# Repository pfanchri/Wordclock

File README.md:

# Wordclock
Mein Projekt für die DIY Vorlesung an der FAU Erlangen

Ziel des Projektes war es eine Wordclock zu erstellen, die kleiner als alle gewöhnlichen Wordclocks ist und als Tischuhr 
fungieren soll. Als Vorbild diente das Modell von qlocktwo. 

Die Uhr kann nicht nur die Zeit anzeigen, sonder speichert auch den Wochentag, dieser wird in der aktuellen Softwareversion 
aber noch nicht angezeigt. Weitere Verbesserungen sind etwa ein Batteriebuffer und weitere Möglichkeiten für die Frontplatte.

Bei der Vorlesung DIY gab es auch ein Wiki für alle Projekte. Das Wordlcock-Projekt ist unter folgendem Link zu finden: 
http://faui7pi.informatik.uni-erlangen.de/mediawiki/index.php/Wordclock

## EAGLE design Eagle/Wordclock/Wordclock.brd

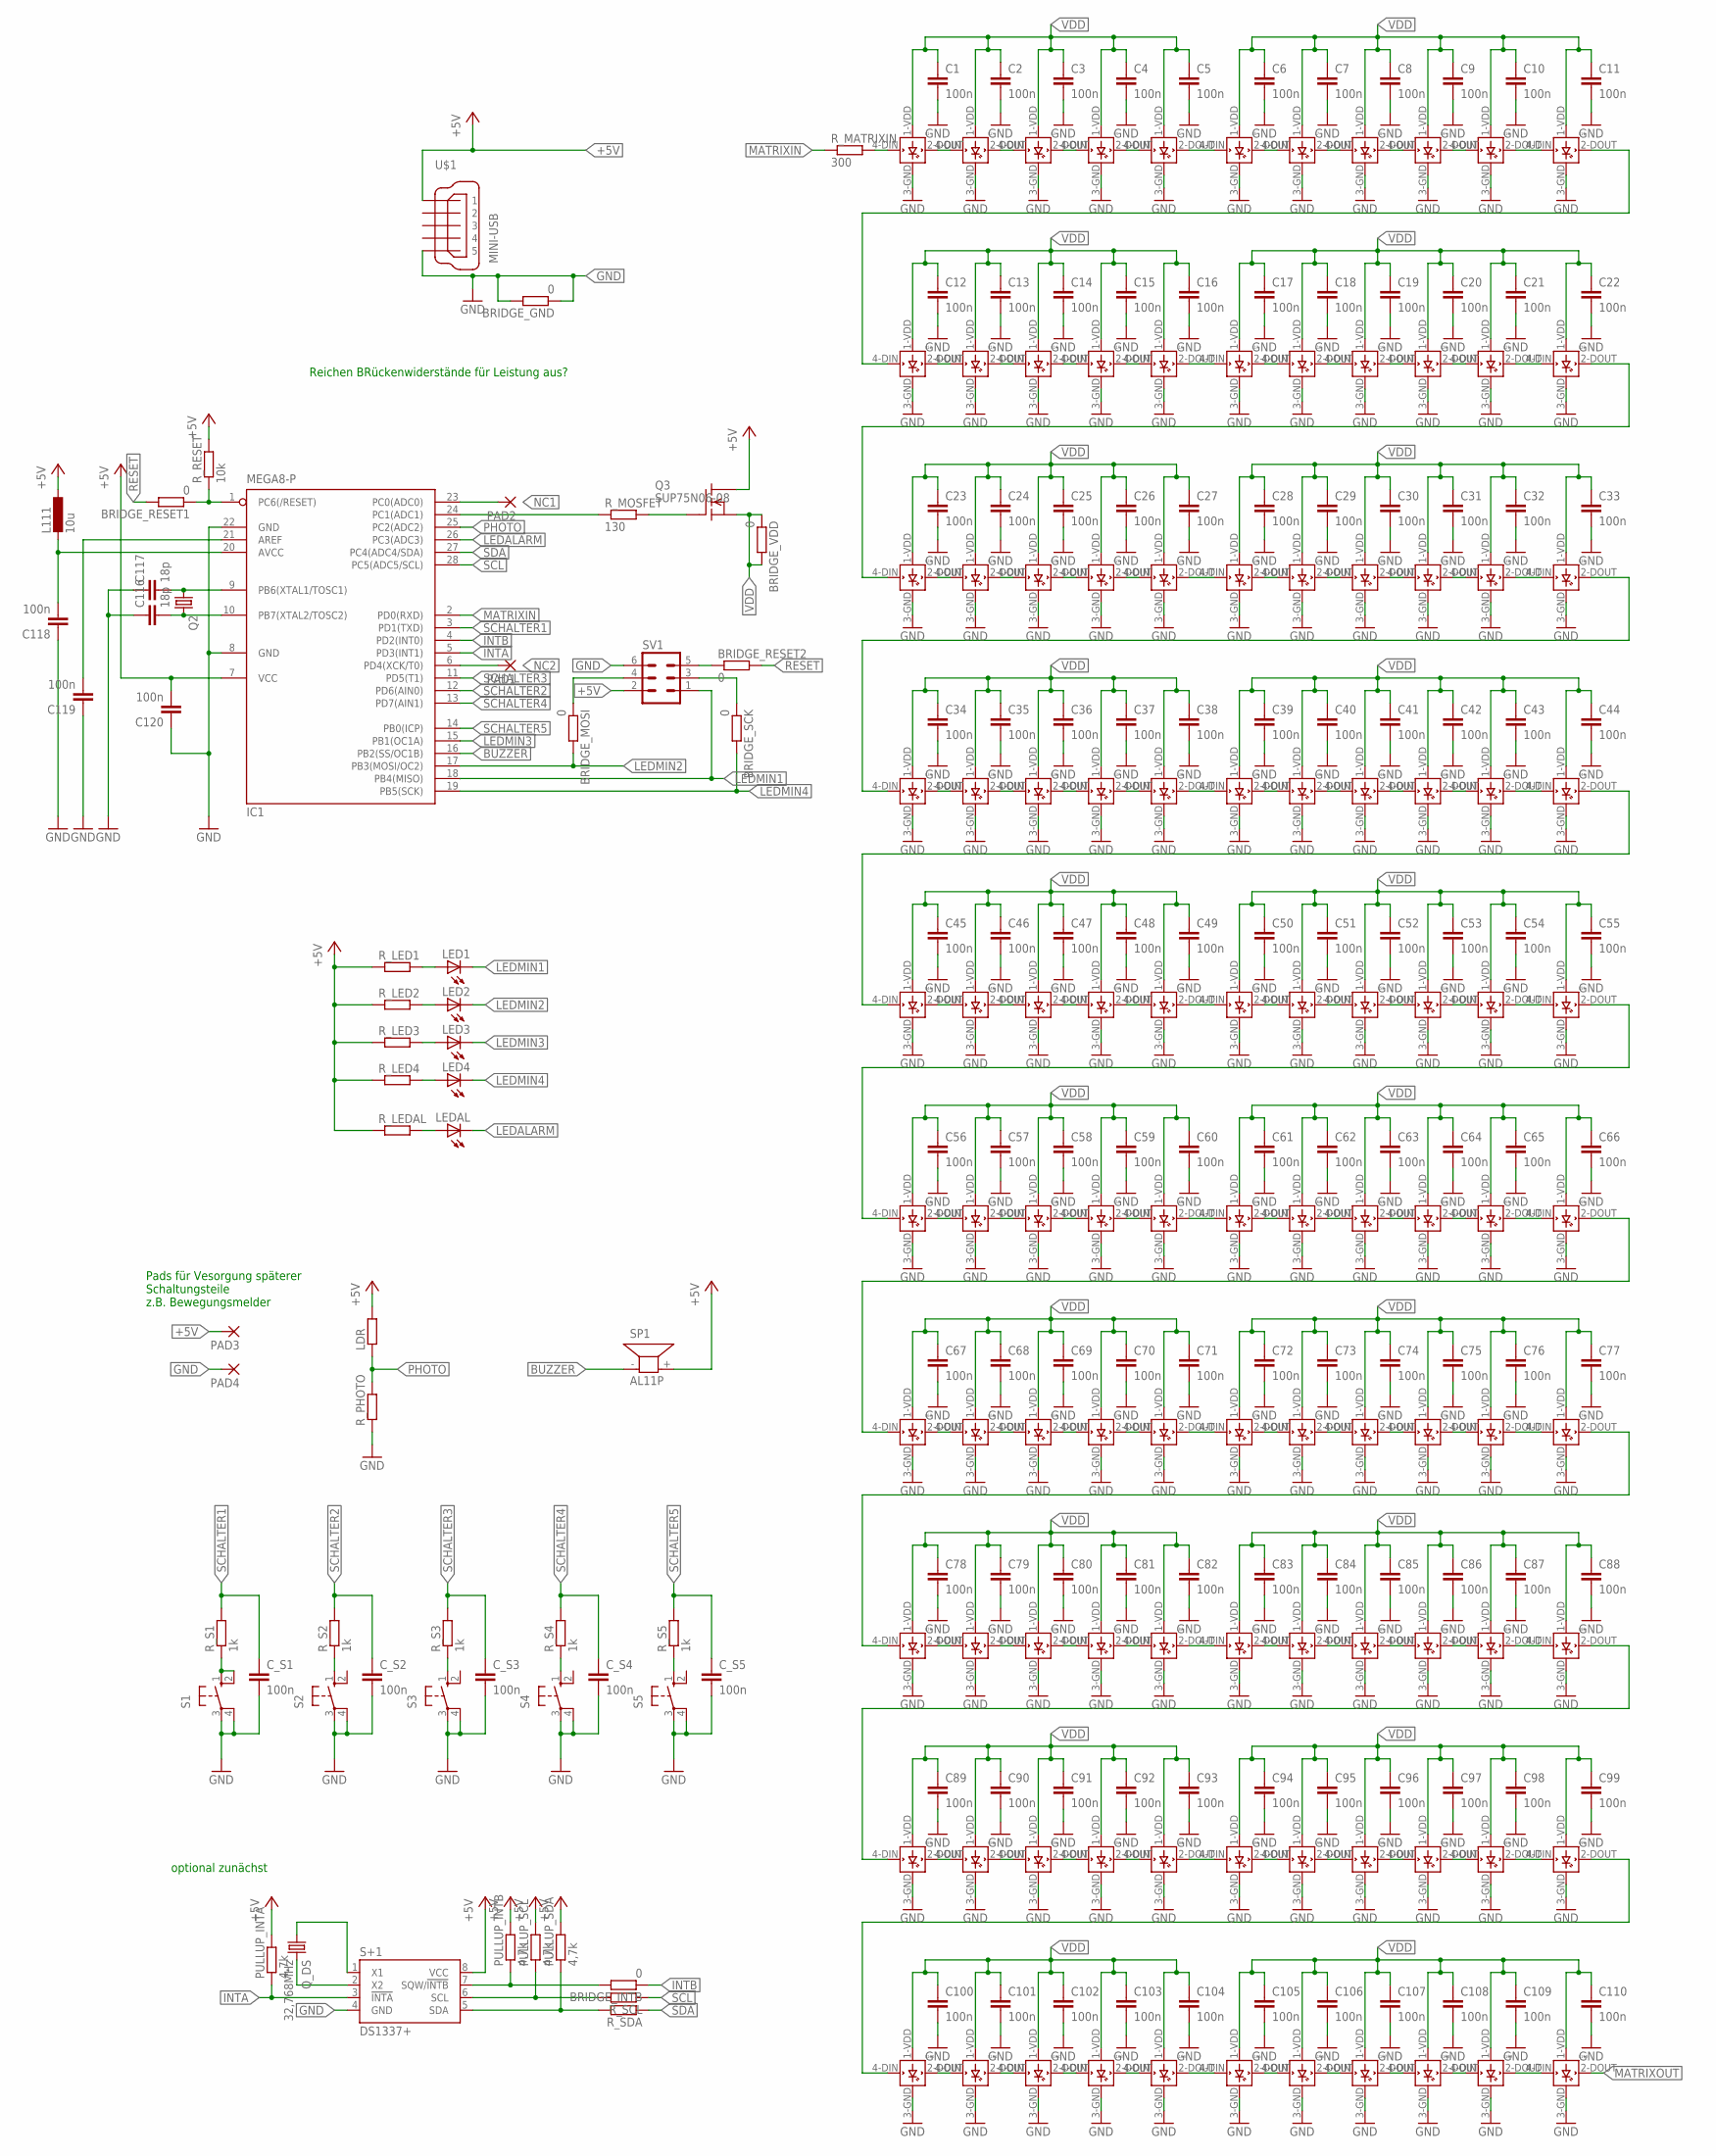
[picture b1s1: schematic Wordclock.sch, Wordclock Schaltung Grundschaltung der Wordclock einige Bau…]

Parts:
BRIDGE_GND: 0; R1206
BRIDGE_INTB: 0; R1206
BRIDGE_MOSI: 0; R1206
BRIDGE_RESET1: 0; M1206
BRIDGE_RESET2: 0; R1206
BRIDGE_SCK: 0; R1206
BRIDGE_VDD: 0; R1206
C1, C2, C3, C4, C5, C6, C7, C8, C9, C10, C11, C12, C13, C14, C15, C16, C17, C18, C19, C20, C21, C22, C23, C24, C25, C26, C27, C28, C29, C30, C31, C32, C33, C34, C35, C36, C37, C38, C39, C40, C41, C42, C43, C44, C45, C46, C47, C48, C49, C50, C51, C52, C53, C54, C55, C56, C57, C58, C59, C60, C61, C62, C63, C64, C65, C66, C67, C68, C69, C70, C71, C72, C73, C74, C75, C76, C77, C78, C79, C80, C81, C82, C83, C84, C85, C86, C87, C88, C89, C90, C91, C92, C93, C94, C95, C96, C97, C98, C99, C100, C101, C102, C103, C104, C105, C106, C107, C108, C109, C110: 100n; C1310
C116, C117: 18p; C0805
C118: 100n; C1206
C119, C120: 100n; C0805
C_S1, C_S2, C_S3, C_S4, C_S5: 100n; C1206
IC1: MEGA8-P; DIL28-3
L1, L2, L3, L4, L5, L6, L7, L8, L9, L10, L11, L12, L13, L14, L15, L16, L17, L18, L19, L20, L21, L22, L23, L24, L25, L26, L27, L28, L29, L30, L31, L32, L33, L34, L35, L36, L37, L38, L39, L40, L41, L42, L43, L44, L45, L46, L47, L48, L49, L50, L51, L52, L53, L54, L55, L56, L57, L58, L59, L60, L61, L62, L63, L64, L65, L66, L67, L68, L69, L70, L71, L72, L73, L74, L75, L76, L77, L78, L79, L80, L81, L82, L83, L84, L85, L86, L87, L88, L89, L90, L91, L92, L93, L94, L95, L96, L97, L98, L99, L100, L101, L102, L103, L104, L105, L106, L107, L108, L109, L110: WS2812B
L111: 10u; L2012C
LDR: R-EU_0204/5; 0204/5
LED1, LED2, LED3, LED4: LEDCHIPLED_1206; CHIPLED_1206
LEDAL: LEDCHIPLED_1206; CHIPLED_1206
PAD1, PAD2, PAD3, PAD4: 2,54/1,1
PULLUP_INTA: 4,7k; R1206
PULLUP_INTB: 4,7k; R1206
PULLUP_SCL: 4,7k; R1206
PULLUP_SDA: 4,7k; R1206
Q2: CRYSTALHC49S; HC49/S
Q3: SUP75N06-08; TO220
Q_DS: 32,768MHz; HC49/S
R_LED1, R_LED2, R_LED3, R_LED4: R-EU_M1206; M1206
R_LEDAL: R-EU_M1206; M1206
R_MATRIXIN: 300; R1206
R_MOSFET: 130; R1206
R_PHOTO: R-EU_M1206; M1206
R_RESET: 10k; M1206
R_S1, R_S2, R_S3, R_S4, R_S5: 1k; M1206
R_SCL: R-EU_R1206; R1206
R_SDA: R-EU_R1206; R1206
S1, S2, S3, S4, S5: 10-XX; B3F-10XX
S+1: DS1337+; DIL8
SP1: AL11P
SV1: ML6L
U$1: MINI-USB

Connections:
+5V: C120.2, IC1.7 (VCC), L111.1, LDR.2, PAD3.1, PULLUP_INTA.2, PULLUP_INTB.2, PULLUP_SCL.2, PULLUP_SDA.2, Q3.2 (D), R_LED1.1, R_LED2.1, R_LED3.1, R_LED4.1, R_LEDAL.1, R_RESET.2, S+1.8 (VCC), SP1.+ (2), SV1.2, U$1.1
BUZZER: IC1.16 (PB2(SS/OC1B)), SP1.- (1)
GND: BRIDGE_GND.1, BRIDGE_GND.2, C1.2, C2.2, C3.2, C4.2, C5.2, C6.2, C7.2, C8.2, C9.2, C10.2, C11.2, C12.2, C13.2, C14.2, C15.2, C16.2, C17.2, C18.2, C19.2, C20.2, C21.2, C22.2, C23.2, C24.2, C25.2, C26.2, C27.2, C28.2, C29.2, C30.2, C31.2, C32.2, C33.2, C34.2, C35.2, C36.2, C37.2, C38.2, C39.2, C40.2, C41.2, C42.2, C43.2, C44.2, C45.2, C46.2, C47.2, C48.2, C49.2, C50.2, C51.2, C52.2, C53.2, C54.2, C55.2, C56.2, C57.2, C58.2, C59.2, C60.2, C61.2, C62.2, C63.2, C64.2, C65.2, C66.2, C67.2, C68.2, C69.2, C70.2, C71.2, C72.2, C73.2, C74.2, C75.2, C76.2, C77.2, C78.2, C79.2, C80.2, C81.2, C82.2, C83.2, C84.2, C85.2, C86.2, C87.2, C88.2, C89.2, C90.2, C91.2, C92.2, C93.2, C94.2, C95.2, C96.2, C97.2, C98.2, C99.2, C100.2, C101.2, C102.2, C103.2, C104.2, C105.2, C106.2, C107.2, C108.2, C109.2, C110.2, C116.1, C117.1, C118.1, C119.1, C120.1, C_S1.2, C_S2.2, C_S3.2, C_S4.2, C_S5.2, IC1.8 (GND), IC1.22 (GND), L1.3-GND (GND), L2.3-GND (GND), L3.3-GND (GND), L4.3-GND (GND), L5.3-GND (GND), L6.3-GND (GND), L7.3-GND (GND), L8.3-GND (GND), L9.3-GND (GND), L10.3-GND (GND), L11.3-GND (GND), L12.3-GND (GND), L13.3-GND (GND), L14.3-GND (GND), L15.3-GND (GND), L16.3-GND (GND), L17.3-GND (GND), L18.3-GND (GND), L19.3-GND (GND), L20.3-GND (GND), L21.3-GND (GND), L22.3-GND (GND), L23.3-GND (GND), L24.3-GND (GND), L25.3-GND (GND), L26.3-GND (GND), L27.3-GND (GND), L28.3-GND (GND), L29.3-GND (GND), L30.3-GND (GND), L31.3-GND (GND), L32.3-GND (GND), L33.3-GND (GND), L34.3-GND (GND), L35.3-GND (GND), L36.3-GND (GND), L37.3-GND (GND), L38.3-GND (GND), L39.3-GND (GND), L40.3-GND (GND), L41.3-GND (GND), L42.3-GND (GND), L43.3-GND (GND), L44.3-GND (GND), L45.3-GND (GND), L46.3-GND (GND), L47.3-GND (GND), L48.3-GND (GND), L49.3-GND (GND), L50.3-GND (GND), L51.3-GND (GND), L52.3-GND (GND), L53.3-GND (GND), L54.3-GND (GND), L55.3-GND (GND), L56.3-GND (GND), L57.3-GND (GND), L58.3-GND (GND), L59.3-GND (GND), L60.3-GND (GND), L61.3-GND (GND), L62.3-GND (GND), L63.3-GND (GND), L64.3-GND (GND), L65.3-GND (GND), L66.3-GND (GND), L67.3-GND (GND), L68.3-GND (GND), L69.3-GND (GND), L70.3-GND (GND), L71.3-GND (GND), L72.3-GND (GND), L73.3-GND (GND), L74.3-GND (GND), L75.3-GND (GND), L76.3-GND (GND), L77.3-GND (GND), L78.3-GND (GND), L79.3-GND (GND), L80.3-GND (GND), L81.3-GND (GND), L82.3-GND (GND), L83.3-GND (GND), L84.3-GND (GND), L85.3-GND (GND), L86.3-GND (GND), L87.3-GND (GND), L88.3-GND (GND), L89.3-GND (GND), L90.3-GND (GND), L91.3-GND (GND), L92.3-GND (GND), L93.3-GND (GND), L94.3-GND (GND), L95.3-GND (GND), L96.3-GND (GND), L97.3-GND (GND), L98.3-GND (GND), L99.3-GND (GND), L100.3-GND (GND), L101.3-GND (GND), L102.3-GND (GND), L103.3-GND (GND), L104.3-GND (GND), L105.3-GND (GND), L106.3-GND (GND), L107.3-GND (GND), L108.3-GND (GND), L109.3-GND (GND), L110.3-GND (GND), PAD4.1, R_PHOTO.1, S1.3, S1.4 (P1), S2.3, S2.4 (P1), S3.3, S3.4 (P1), S4.3, S4.4 (P1), S5.3, S5.4 (P1), S+1.4 (GND), SV1.6, U$1.5
INTA: IC1.5 (PD3(INT1)), PULLUP_INTA.1, S+1.3 (!INTA)
INTB: BRIDGE_INTB.1, IC1.4 (PD2(INT0))
INTB_UNBRIDGED: BRIDGE_INTB.2, PULLUP_INTB.1, S+1.7 (SQW/!INTB!)
LEDALARM: IC1.26 (PC3(ADC3)), LEDAL.C
LEDMIN1: IC1.18 (PB4(MISO)), LED1.C, SV1.1
LEDMIN2: BRIDGE_MOSI.2, IC1.17 (PB3(MOSI/OC2)), LED2.C
LEDMIN3: IC1.15 (PB1(OC1A)), LED3.C
LEDMIN4: BRIDGE_SCK.2, IC1.19 (PB5(SCK)), LED4.C
MATRIXIN: IC1.2 (PD0(RXD)), R_MATRIXIN.1
MATRIXOUT: L110.2-DOUT (DOUT)
MOSFET_A: IC1.24 (PC1(ADC1)), R_MOSFET.1
MOSFET_B: Q3.1 (G), R_MOSFET.2
unnamed: L1.2-DOUT (DOUT), L2.4-DIN (DIN)
unnamed: L2.2-DOUT (DOUT), L3.4-DIN (DIN)
unnamed: L3.2-DOUT (DOUT), L4.4-DIN (DIN)
unnamed: L4.2-DOUT (DOUT), L5.4-DIN (DIN)
unnamed: L6.2-DOUT (DOUT), L7.4-DIN (DIN)
unnamed: L5.2-DOUT (DOUT), L6.4-DIN (DIN)
unnamed: L7.2-DOUT (DOUT), L8.4-DIN (DIN)
unnamed: L8.2-DOUT (DOUT), L9.4-DIN (DIN)
unnamed: L9.2-DOUT (DOUT), L10.4-DIN (DIN)
unnamed: L10.2-DOUT (DOUT), L11.4-DIN (DIN)
unnamed: L12.2-DOUT (DOUT), L13.4-DIN (DIN)
unnamed: L13.2-DOUT (DOUT), L14.4-DIN (DIN)
unnamed: L14.2-DOUT (DOUT), L15.4-DIN (DIN)
unnamed: L15.2-DOUT (DOUT), L16.4-DIN (DIN)
unnamed: L16.2-DOUT (DOUT), L17.4-DIN (DIN)
unnamed: L17.2-DOUT (DOUT), L18.4-DIN (DIN)
unnamed: L18.2-DOUT (DOUT), L19.4-DIN (DIN)
unnamed: L19.2-DOUT (DOUT), L20.4-DIN (DIN)
unnamed: L20.2-DOUT (DOUT), L21.4-DIN (DIN)
unnamed: Q_DS.1, S+1.1 (X1)
unnamed: Q_DS.2, S+1.2 (X2)
unnamed: L21.2-DOUT (DOUT), L22.4-DIN (DIN)
unnamed: L23.2-DOUT (DOUT), L24.4-DIN (DIN)
unnamed: L24.2-DOUT (DOUT), L25.4-DIN (DIN)
unnamed: L25.2-DOUT (DOUT), L26.4-DIN (DIN)
unnamed: L26.2-DOUT (DOUT), L27.4-DIN (DIN)
unnamed: L27.2-DOUT (DOUT), L28.4-DIN (DIN)
unnamed: L28.2-DOUT (DOUT), L29.4-DIN (DIN)
unnamed: L29.2-DOUT (DOUT), L30.4-DIN (DIN)
unnamed: L30.2-DOUT (DOUT), L31.4-DIN (DIN)
unnamed: L31.2-DOUT (DOUT), L32.4-DIN (DIN)
unnamed: L32.2-DOUT (DOUT), L33.4-DIN (DIN)
unnamed: L34.2-DOUT (DOUT), L35.4-DIN (DIN)
unnamed: L35.2-DOUT (DOUT), L36.4-DIN (DIN)
unnamed: L36.2-DOUT (DOUT), L37.4-DIN (DIN)
unnamed: L37.2-DOUT (DOUT), L38.4-DIN (DIN)
unnamed: L38.2-DOUT (DOUT), L39.4-DIN (DIN)
unnamed: L39.2-DOUT (DOUT), L40.4-DIN (DIN)
unnamed: L40.2-DOUT (DOUT), L41.4-DIN (DIN)
unnamed: L41.2-DOUT (DOUT), L42.4-DIN (DIN)
unnamed: L42.2-DOUT (DOUT), L43.4-DIN (DIN)
unnamed: L43.2-DOUT (DOUT), L44.4-DIN (DIN)
unnamed: L45.2-DOUT (DOUT), L46.4-DIN (DIN)
unnamed: L46.2-DOUT (DOUT), L47.4-DIN (DIN)
unnamed: L47.2-DOUT (DOUT), L48.4-DIN (DIN)
unnamed: L48.2-DOUT (DOUT), L49.4-DIN (DIN)
unnamed: L49.2-DOUT (DOUT), L50.4-DIN (DIN)
unnamed: L50.2-DOUT (DOUT), L51.4-DIN (DIN)
unnamed: L51.2-DOUT (DOUT), L52.4-DIN (DIN)
unnamed: L52.2-DOUT (DOUT), L53.4-DIN (DIN)
unnamed: L53.2-DOUT (DOUT), L54.4-DIN (DIN)
unnamed: L54.2-DOUT (DOUT), L55.4-DIN (DIN)
unnamed: L56.2-DOUT (DOUT), L57.4-DIN (DIN)
unnamed: L57.2-DOUT (DOUT), L58.4-DIN (DIN)
unnamed: L58.2-DOUT (DOUT), L59.4-DIN (DIN)
unnamed: L59.2-DOUT (DOUT), L60.4-DIN (DIN)
unnamed: L60.2-DOUT (DOUT), L61.4-DIN (DIN)
unnamed: L61.2-DOUT (DOUT), L62.4-DIN (DIN)
unnamed: L62.2-DOUT (DOUT), L63.4-DIN (DIN)
unnamed: L63.2-DOUT (DOUT), L64.4-DIN (DIN)
unnamed: L64.2-DOUT (DOUT), L65.4-DIN (DIN)
unnamed: L65.2-DOUT (DOUT), L66.4-DIN (DIN)
unnamed: L67.2-DOUT (DOUT), L68.4-DIN (DIN)
unnamed: L68.2-DOUT (DOUT), L69.4-DIN (DIN)
unnamed: L69.2-DOUT (DOUT), L70.4-DIN (DIN)
unnamed: L70.2-DOUT (DOUT), L71.4-DIN (DIN)
unnamed: L71.2-DOUT (DOUT), L72.4-DIN (DIN)
unnamed: L72.2-DOUT (DOUT), L73.4-DIN (DIN)
unnamed: L73.2-DOUT (DOUT), L74.4-DIN (DIN)
unnamed: L74.2-DOUT (DOUT), L75.4-DIN (DIN)
unnamed: L75.2-DOUT (DOUT), L76.4-DIN (DIN)
unnamed: L76.2-DOUT (DOUT), L77.4-DIN (DIN)
unnamed: L78.2-DOUT (DOUT), L79.4-DIN (DIN)
unnamed: L79.2-DOUT (DOUT), L80.4-DIN (DIN)
unnamed: L80.2-DOUT (DOUT), L81.4-DIN (DIN)
unnamed: L81.2-DOUT (DOUT), L82.4-DIN (DIN)
unnamed: L82.2-DOUT (DOUT), L83.4-DIN (DIN)
unnamed: L83.2-DOUT (DOUT), L84.4-DIN (DIN)
unnamed: L84.2-DOUT (DOUT), L85.4-DIN (DIN)
unnamed: L85.2-DOUT (DOUT), L86.4-DIN (DIN)
unnamed: L86.2-DOUT (DOUT), L87.4-DIN (DIN)
unnamed: L87.2-DOUT (DOUT), L88.4-DIN (DIN)
unnamed: L89.2-DOUT (DOUT), L90.4-DIN (DIN)
unnamed: L90.2-DOUT (DOUT), L91.4-DIN (DIN)
unnamed: L91.2-DOUT (DOUT), L92.4-DIN (DIN)
unnamed: L92.2-DOUT (DOUT), L93.4-DIN (DIN)
unnamed: L93.2-DOUT (DOUT), L94.4-DIN (DIN)
unnamed: L94.2-DOUT (DOUT), L95.4-DIN (DIN)
unnamed: L95.2-DOUT (DOUT), L96.4-DIN (DIN)
unnamed: L96.2-DOUT (DOUT), L97.4-DIN (DIN)
unnamed: L97.2-DOUT (DOUT), L98.4-DIN (DIN)
unnamed: L98.2-DOUT (DOUT), L99.4-DIN (DIN)
unnamed: L100.2-DOUT (DOUT), L101.4-DIN (DIN)
unnamed: L101.2-DOUT (DOUT), L102.4-DIN (DIN)
unnamed: L102.2-DOUT (DOUT), L103.4-DIN (DIN)
unnamed: L103.2-DOUT (DOUT), L104.4-DIN (DIN)
unnamed: L104.2-DOUT (DOUT), L105.4-DIN (DIN)
unnamed: L105.2-DOUT (DOUT), L106.4-DIN (DIN)
unnamed: L106.2-DOUT (DOUT), L107.4-DIN (DIN)
unnamed: L107.2-DOUT (DOUT), L108.4-DIN (DIN)
unnamed: L108.2-DOUT (DOUT), L109.4-DIN (DIN)
unnamed: L109.2-DOUT (DOUT), L110.4-DIN (DIN)
unnamed: L11.2-DOUT (DOUT), L12.4-DIN (DIN)
unnamed: L22.2-DOUT (DOUT), L23.4-DIN (DIN)
unnamed: L33.2-DOUT (DOUT), L34.4-DIN (DIN)
unnamed: L44.2-DOUT (DOUT), L45.4-DIN (DIN)
unnamed: L55.2-DOUT (DOUT), L56.4-DIN (DIN)
unnamed: L66.2-DOUT (DOUT), L67.4-DIN (DIN)
unnamed: L77.2-DOUT (DOUT), L78.4-DIN (DIN)
unnamed: L88.2-DOUT (DOUT), L89.4-DIN (DIN)
unnamed: L99.2-DOUT (DOUT), L100.4-DIN (DIN)
unnamed: PULLUP_SCL.1, R_SCL.2, S+1.6 (SCL)
unnamed: C118.2, IC1.20 (AVCC), L111.2
unnamed: LED1.A, R_LED1.2
unnamed: LED2.A, R_LED2.2
unnamed: LED3.A, R_LED3.2
unnamed: LED4.A, R_LED4.2
unnamed: LEDAL.A, R_LEDAL.2
unnamed: R_S1.1, S1.1 (S), S1.2 (S1)
unnamed: R_S2.1, S2.1 (S)
unnamed: R_S3.1, S3.1 (S)
unnamed: R_S4.1, S4.1 (S)
unnamed: C119.2, IC1.21 (AREF)
unnamed: PULLUP_SDA.1, R_SDA.2, S+1.5 (SDA)
unnamed: BRIDGE_RESET1.1, IC1.1 (PC6(/RESET)), R_RESET.1
unnamed: R_S5.1, S5.1 (S)
unnamed: BRIDGE_MOSI.1, SV1.4
unnamed: BRIDGE_SCK.1, SV1.3
unnamed: BRIDGE_RESET2.1, SV1.5
unnamed: L1.4-DIN (DIN), R_MATRIXIN.2
unnamed: C117.2, IC1.9 (PB6(XTAL1/TOSC1)), Q2.1
unnamed: C116.2, IC1.10 (PB7(XTAL2/TOSC2)), Q2.2
NC1: IC1.23 (PC0(ADC0)), PAD2.1
NC2: IC1.6 (PD4(XCK/T0)), PAD1.1
PHOTO: IC1.25 (PC2(ADC2)), LDR.1, R_PHOTO.2
RESET: BRIDGE_RESET1.2, BRIDGE_RESET2.2
SCHALTER1: C_S1.1, IC1.3 (PD1(TXD)), R_S1.2
SCHALTER2: C_S2.1, IC1.12 (PD6(AIN0)), R_S2.2
SCHALTER3: C_S3.1, IC1.11 (PD5(T1)), R_S3.2
SCHALTER4: C_S4.1, IC1.13 (PD7(AIN1)), R_S4.2
SCHALTER5: C_S5.1, IC1.14 (PB0(ICP)), R_S5.2
SCL: IC1.28 (PC5(ADC5/SCL)), R_SCL.1
SDA: IC1.27 (PC4(ADC4/SDA)), R_SDA.1
VDD: BRIDGE_VDD.1, BRIDGE_VDD.2, C1.1, C2.1, C3.1, C4.1, C5.1, C6.1, C7.1, C8.1, C9.1, C10.1, C11.1, C12.1, C13.1, C14.1, C15.1, C16.1, C17.1, C18.1, C19.1, C20.1, C21.1, C22.1, C23.1, C24.1, C25.1, C26.1, C27.1, C28.1, C29.1, C30.1, C31.1, C32.1, C33.1, C34.1, C35.1, C36.1, C37.1, C38.1, C39.1, C40.1, C41.1, C42.1, C43.1, C44.1, C45.1, C46.1, C47.1, C48.1, C49.1, C50.1, C51.1, C52.1, C53.1, C54.1, C55.1, C56.1, C57.1, C58.1, C59.1, C60.1, C61.1, C62.1, C63.1, C64.1, C65.1, C66.1, C67.1, C68.1, C69.1, C70.1, C71.1, C72.1, C73.1, C74.1, C75.1, C76.1, C77.1, C78.1, C79.1, C80.1, C81.1, C82.1, C83.1, C84.1, C85.1, C86.1, C87.1, C88.1, C89.1, C90.1, C91.1, C92.1, C93.1, C94.1, C95.1, C96.1, C97.1, C98.1, C99.1, C100.1, C101.1, C102.1, C103.1, C104.1, C105.1, C106.1, C107.1, C108.1, C109.1, C110.1, L1.1-VDD (VDD), L2.1-VDD (VDD), L3.1-VDD (VDD), L4.1-VDD (VDD), L5.1-VDD (VDD), L6.1-VDD (VDD), L7.1-VDD (VDD), L8.1-VDD (VDD), L9.1-VDD (VDD), L10.1-VDD (VDD), L11.1-VDD (VDD), L12.1-VDD (VDD), L13.1-VDD (VDD), L14.1-VDD (VDD), L15.1-VDD (VDD), L16.1-VDD (VDD), L17.1-VDD (VDD), L18.1-VDD (VDD), L19.1-VDD (VDD), L20.1-VDD (VDD), L21.1-VDD (VDD), L22.1-VDD (VDD), L23.1-VDD (VDD), L24.1-VDD (VDD), L25.1-VDD (VDD), L26.1-VDD (VDD), L27.1-VDD (VDD), L28.1-VDD (VDD), L29.1-VDD (VDD), L30.1-VDD (VDD), L31.1-VDD (VDD), L32.1-VDD (VDD), L33.1-VDD (VDD), L34.1-VDD (VDD), L35.1-VDD (VDD), L36.1-VDD (VDD), L37.1-VDD (VDD), L38.1-VDD (VDD), L39.1-VDD (VDD), L40.1-VDD (VDD), L41.1-VDD (VDD), L42.1-VDD (VDD), L43.1-VDD (VDD), L44.1-VDD (VDD), L45.1-VDD (VDD), L46.1-VDD (VDD), L47.1-VDD (VDD), L48.1-VDD (VDD), L49.1-VDD (VDD), L50.1-VDD (VDD), L51.1-VDD (VDD), L52.1-VDD (VDD), L53.1-VDD (VDD), L54.1-VDD (VDD), L55.1-VDD (VDD), L56.1-VDD (VDD), L57.1-VDD (VDD), L58.1-VDD (VDD), L59.1-VDD (VDD), L60.1-VDD (VDD), L61.1-VDD (VDD), L62.1-VDD (VDD), L63.1-VDD (VDD), L64.1-VDD (VDD), L65.1-VDD (VDD), L66.1-VDD (VDD), L67.1-VDD (VDD), L68.1-VDD (VDD), L69.1-VDD (VDD), L70.1-VDD (VDD), L71.1-VDD (VDD), L72.1-VDD (VDD), L73.1-VDD (VDD), L74.1-VDD (VDD), L75.1-VDD (VDD), L76.1-VDD (VDD), L77.1-VDD (VDD), L78.1-VDD (VDD), L79.1-VDD (VDD), L80.1-VDD (VDD), L81.1-VDD (VDD), L82.1-VDD (VDD), L83.1-VDD (VDD), L84.1-VDD (VDD), L85.1-VDD (VDD), L86.1-VDD (VDD), L87.1-VDD (VDD), L88.1-VDD (VDD), L89.1-VDD (VDD), L90.1-VDD (VDD), L91.1-VDD (VDD), L92.1-VDD (VDD), L93.1-VDD (VDD), L94.1-VDD (VDD), L95.1-VDD (VDD), L96.1-VDD (VDD), L97.1-VDD (VDD), L98.1-VDD (VDD), L99.1-VDD (VDD), L100.1-VDD (VDD), L101.1-VDD (VDD), L102.1-VDD (VDD), L103.1-VDD (VDD), L104.1-VDD (VDD), L105.1-VDD (VDD), L106.1-VDD (VDD), L107.1-VDD (VDD), L108.1-VDD (VDD), L109.1-VDD (VDD), L110.1-VDD (VDD), Q3.3 (S)

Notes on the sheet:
optional zunächst
Reichen BRückenwiderstände für Leistung aus?
Pads für Vesorgung späterer Schaltungsteile z.B. Bewegungsmelder

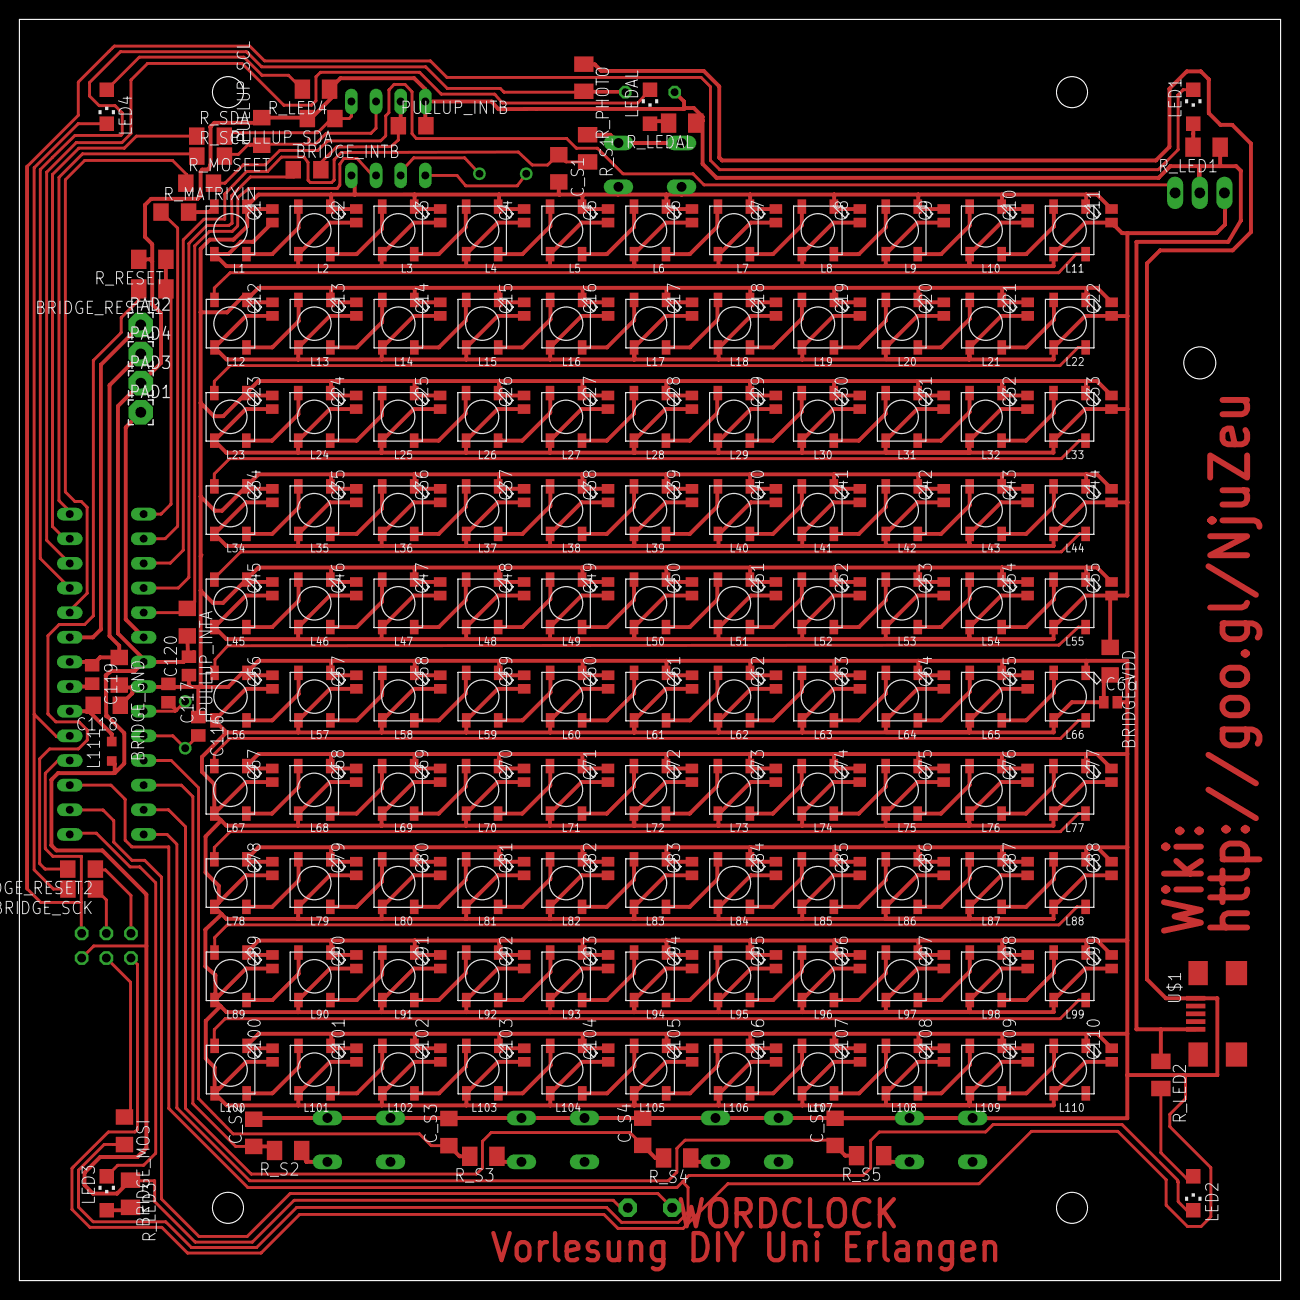
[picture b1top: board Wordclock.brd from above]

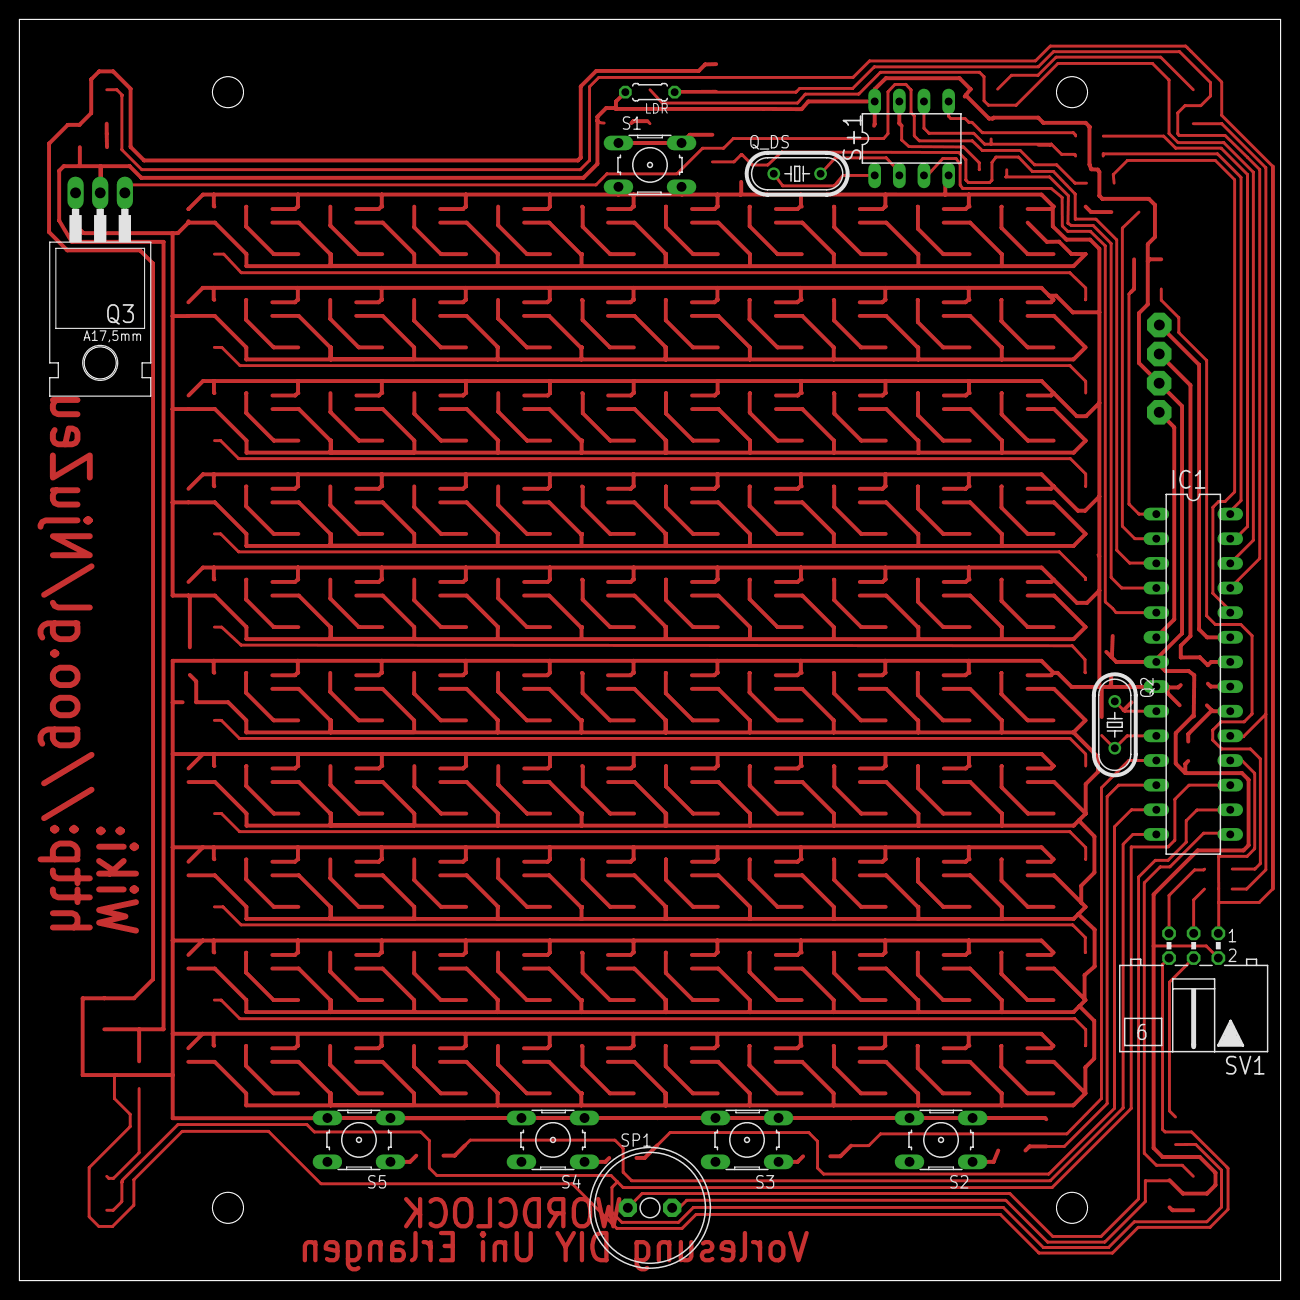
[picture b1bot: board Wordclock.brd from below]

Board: 2 copper layers, 130.0 x 130.0 mm, 281 parts (13 on the bottom side), 158 nets.

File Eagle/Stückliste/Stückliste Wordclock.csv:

"Qty";"Value";"Device";"Package";"Parts";"Description";"MF";"MPN";"OC_FARNELL";"OC_NEWARK";
"5";"";"10-XX";"B3F-10XX";"S1, S2, S3, S4, S5";"OMRON SWITCH";"";"B3F-1000";"176432";"36M3542";
"4";"";"2,54/1,1";"2,54/1,1";"PAD1, PAD2, PAD3, PAD4";"THROUGH-HOLE PAD";"";"";"";"";
"1";"";"CRYSTALHC49S";"HC49/S";"Q2";"CRYSTAL";"";"";"1667008";"unknown";
"5";"";"LEDCHIPLED_1206";"CHIPLED_1206";"LED1, LED2, LED3, LED4, LEDAL";"LED";"";"";"";"";
"1";"";"ML6L";"ML6L";"SV1";"HARTING";"";"";"unknown";"unknown";
"1";"";"R-EU_0204/5";"0204/5";"LDR";"RESISTOR, European symbol";"";"";"";"";
"1";"0";"R-EU_M1206";"M1206";"BRIDGE_RESET1";"RESISTOR, European symbol";"";"";"";"";
"8";"0";"R-EU_R1206";"R1206";"BRIDGE_GND, BRIDGE_INTB, BRIDGE_MOSI, BRIDGE_RESET2, BRIDGE_SCK, BRIDGE_VDD, R_SCL, R_SDA";"RESISTOR, European symbol";"";"";"";"";
"2";"100n";"C-EUC0805";"C0805";"C119, C120";"CAPACITOR, European symbol";"";"";"";"";
"6";"100n";"C-EUC1206";"C1206";"C118, C_S1, C_S2, C_S3, C_S4, C_S5";"CAPACITOR, European symbol";"";"";"";"";
"110";"100n";"C-EUC1310";"C1310";"C1, C2, C3, C4, C5, C6, C7, C8, C9, C10, C11, C12, C13, C14, C15, C16, C17, C18, C19, C20, C21, C22, C23, C24, C25, C26, C27, C28, C29, C30, C31, C32, C33, C34, C35, C36, C37, C38, C39, C40, C41, C42, C43, C44, C45, C46, C47, C48, C49, C50, C51, C52, C53, C54, C55, C56, C57, C58, C59, C60, C61, C62, C63, C64, C65, C66, C67, C68, C69, C70, C71, C72, C73, C74, C75, C76, C77, C78, C79, C80, C81, C82, C83, C84, C85, C86, C87, C88, C89, C90, C91, C92, C93, C94, C95, C96, C97, C98, C99, C100, C101, C102, C103, C104, C105, C106, C107, C108, C109, C110";"CAPACITOR, European symbol";"";"";"";"";
"1";"10k";"R-EU_M1206";"M1206";"R_RESET";"RESISTOR, European symbol";"";"";"";"";
"1";"10u";"L-EUL2012C";"L2012C";"L111";"INDUCTOR, European symbol";"";"";"";"";
"5";"120";"R-EU_M1206";"M1206";"R_LED1, R_LED2, R_LED3, R_LED4, R_LEDAL";"RESISTOR, European symbol";"";"";"";"";
"1";"130";"R-EU_R1206";"R1206";"R_MOSFET";"RESISTOR, European symbol";"";"";"";"";
"2";"18p";"C-EUC0805";"C0805";"C116, C117";"CAPACITOR, European symbol";"";"";"";"";
"5";"1k";"R-EU_M1206";"M1206";"R_S1, R_S2, R_S3, R_S4, R_S5";"RESISTOR, European symbol";"";"";"";"";
"1";"300";"R-EU_R1206";"R1206";"R_MATRIXIN";"RESISTOR, European symbol";"";"";"";"";
"1";"32,768MHz";"CRYSTALHC49S";"HC49/S";"Q_DS";"CRYSTAL";"";"";"1667008";"unknown";
"4";"4,7k";"R-EU_R1206";"R1206";"PULLUP_INTA, PULLUP_INTB, PULLUP_SCL, PULLUP_SDA";"RESISTOR, European symbol";"";"";"";"";
"1";"49,9k";"R-EU_M1206";"M1206";"R_PHOTO";"RESISTOR, European symbol";"";"";"";"";
"1";"AL11P";"AL11P";"AL11P";"SP1";"SPEAKER Source: Buerklin";"";"";"unknown";"unknown";
"1";"DS1337+";"DS1337+";"DIL8";"S+1";"DS1337 I2C serial real-time clock";"";"";"";"";
"1";"MEGA8-P";"MEGA8-P";"DIL28-3";"IC1";"MICROCONTROLLER";"";"";"unknown";"unknown";
"1";"MINI-USB";"MINI-USB";"MINI-USB";"U$1";"Mini USB connector (Kyocera part: 24 5141 005 000 863+)";"";"";"";"";
"1";"SUP75N06-08";"SUP75N06-08";"TO220";"Q3";"N-Channel Enhancement MOSFET 60V; 75A; 0,008Ohm";"";"";"";"";
"110";"WS2812B";"WS2812B";"WS2812B";"L1, L2, L3, L4, L5, L6, L7, L8, L9, L10, L11, L12, L13, L14, L15, L16, L17, L18, L19, L20, L21, L22, L23, L24, L25, L26, L27, L28, L29, L30, L31, L32, L33, L34, L35, L36, L37, L38, L39, L40, L41, L42, L43, L44, L45, L46, L47, L48, L49, L50, L51, L52, L53, L54, L55, L56, L57, L58, L59, L60, L61, L62, L63, L64, L65, L66, L67, L68, L69, L70, L71, L72, L73, L74, L75, L76, L77, L78, L79, L80, L81, L82, L83, L84, L85, L86, L87, L88, L89, L90, L91, L92, L93, L94, L95, L96, L97, L98, L99, L100, L101, L102, L103, L104, L105, L106, L107, L108, L109, L110";"";"";"";"";"";

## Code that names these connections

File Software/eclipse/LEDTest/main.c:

/*
 * main.c
 *
 *  Created on: 18.01.2016
 *      Author: christofpfannenmuller
 */
#include <util/delay.h>
#include <avr/io.h>
#include <stdlib.h>
#include <avr/interrupt.h>

#include "light_ws2812.h"

#define t_alarm //TODO: Einfgen der Pins fr die Taster
#define t_up
#define t_down
#define t_snooze
#define t_mode
#define V_ON_B 0  //Wert fr LED on 0...255
#define V_ON_G 30  //Wert fr LED on 0...255
#define V_ON_R 0  //Wert fr LED on 0...255



struct cRGB matrix[10];
uint8_t stunden=1; //aktueller Stundenwert  1...12
uint8_t minuten=0; //aktueller Minutenwert  0...59
uint8_t frontplatte=0; //Art der Frontplatte; 0:Standartfrontplatte; 1:Binre Frontplatte; 2:Englische Frontplatte; ...
uint8_t matrix_on=1;

void setalarm(void){
	//get alarm time from user


	//send alarm time to RTC
}

void settime(void){

	//get time from user Zeit


	//send time to RTC

}

void showtime(uint8_t hours_to_show, uint8_t minutes_to_show){

	//beginn der Frontplattenansteuerung
	if(frontplatte==0){
		//Zeitanzeige fr Standart Frontplatte
		//Minutenleds
		PORTB |= (1<<PB5);PORTB |= (1<<PB4);PORTB |= (1<<PB3);PORTB |= (1<<PB1);//alle Minutenleds off
		switch(minutes_to_show%5) {//setzen entsprechende Minuten auf GND
			case 1: PORTB &=~ (1<<PB4); break;
			case 2: PORTB &=~ (1<<PB4)^(1<<PB3); break;
			case 3: PORTB &=~ (1<<PB4)^(1<<PB3)^(1<<PB1); break;
			case 4: PORTB &=~ (1<<PB4)^(1<<PB3)^(1<<PB1)^(1<<PB5); break;
		}





		/*
		//Leeren des Arrays
		for(uint8_t i=0; i<=110; i++){
			matrix[i].r=0;matrix[i].g=0;matrix[i].b=0;
		}
		//Ansteuerung der Matrix

				Vorlage:
				es ist ein uhr
				es ist fnf nach eins
				es ist zehn nach eins
				es ist viertel zwei
				es ist zehn vor halb zwei
				es ist fnf vor halb zwei
				es ist halb zwei
				es ist fnf nach halb zwei
				es ist zehn nach halb zwei
				es ist dreiviertel zwei
				es ist zehn vor zwei
				es ist fnf vor zwei
				*/


			//ES IST anschalten
		matrix[0].r=V_ON_R;matrix[0].g=V_ON_G;matrix[0].b=V_ON_B;
		matrix[1].r=V_ON_R;matrix[1].g=V_ON_G;matrix[1].b=V_ON_B;
		matrix[3].r=V_ON_R;matrix[3].g=V_ON_G;matrix[3].b=V_ON_B;
		matrix[4].r=V_ON_R;matrix[4].g=V_ON_G;matrix[4].b=V_ON_B;//TODO: ES IST darf nur dann angezeigt werden wenn es das auch soll
		matrix[5].r=V_ON_R;matrix[5].g=V_ON_G;matrix[5].b=V_ON_B;

		//TODO: Anpassen an die aktuellen Ports
		//Minuten anschalten

/*


			switch(((int) (minutes_to_show/5))*5) {
				case 0:PORTD|= (1<<7) ; break;  //x Uhr
				case 5:PORTB|= (1<<1);PORTB|= (1<<7); break; 										//5 nach x
				case 10:PORTB|= (1<<3);PORTB|= (1<<7) ; break; 										//10 nach x
				case 15:PORTB|= (1<<6); hours_to_show++ ; break;      								//viertel x+1
				case 20:PORTB|= (1<<3); PORTA|= (1<<0); PORTA|= (1<<1);hours_to_show++ ; break; 	//zehn vor halb x+1
				case 25:PORTB|= (1<<1); PORTA|= (1<<0); PORTA|= (1<<1);hours_to_show++  ; break;	//fünf vor halb x+1
				case 30:PORTA|= (1<<1);hours_to_show++  ; break; 									//halb x+1
				case 35:PORTB|= (1<<1); PORTB|= (1<<7); PORTA|= (1<<1);hours_to_show++  ; break; 	//fnf nach halb x+1
				case 40:PORTB|= (1<<3); PORTB|= (1<<7); PORTA|= (1<<1);hours_to_show++  ; break; 	//fnf nach halb x+1
				case 45:PORTB|= (1<<5); PORTB|= (1<<6);hours_to_show++ ; break; 					//dreiviertel x+1
				case 50:PORTB|= (1<<3); PORTA|= (1<<0);hours_to_show++ ; break; 					//zehn vor x+1
				case 55:PORTB|= (1<<1); PORTA|= (1<<0);hours_to_show++ ; break; 					//fnf vor x+1
			}
			if (hours_to_show>=13){hours_to_show=1;}
			switch (hours_to_show){
				case 1:	PORTA|= (1<<4);PORTA|= (1<<5);PORTA|= (1<<6);break; 						//EINS
				case 2: PORTA|= (1<<3);PORTA|= (1<<4);break;  										//ZWEI
				case 3: PORTC|= (1<<7);break; 														//DREI
				case 4: PORTC|= (1<<3);break; 														//VIER
				case 5: PORTC|= (1<<6);break; 														//FNF
				case 6: PORTC|= (1<<0);break; 														//SECHS
				case 7: PORTA|= (1<<6);PORTA|= (1<<7);break;  										//SIEBEN
				case 8: PORTC|= (1<<2);break;														//ACHT
				case 9: PORTC|= (1<<4);break;														//NEUN
				case 10: PORTC|= (1<<1);break;														//ZEHN
				case 11: PORTC|= (1<<5);break;														//ELF
				case 12: PORTA|= (1<<2);break;														//ZWLF
			}



			*/


	}else if(frontplatte==1){
		//Zeitanzeige fr Binre Frontplatte
	}else if(frontplatte==2){
		//Zeitanzeige fr Englische Frontplatte
	}
	//Ende der Frontplattenansteuerung

	if(matrix_on){
		PORTC &= ~ (1<<1);							//TODO:Mosfet anschalten

		ws2812_setleds(matrix,10);

		}else{
									//TODO:Mosfet ausschalten
		}
}

void change_frontplatte(uint8_t new_frontplatte){
	frontplatte=new_frontplatte;
}

void init(void){
	//in outputs intit
	//minutenleds + alarmLed
	//setze bit 1 =Ausgang
		DDRB |= (1<<1);
		DDRB |= (1<<3);
		DDRB |= (1<<4);
		DDRB |= (1<<5);
		DDRC |= (1<<3);//AlarmLED
		// setze pin auf vdd = LED aus
		PORTB |= (1<<1);
		PORTB |= (1<<3);
		PORTB |= (1<<4);
		PORTB |= (1<<5);
		PORTC |= (1<<3);//AlarmLED

		//Buzzer als Ausgang setzen und auf +5V schalten = ausgeschaltet
		DDRB |= (1<<2);
		PORTB |= (1<<2);

}

int main(void){
	//itialisierung
	init();
	//settime();//get time from user
	//setalarm();

	//mosefet leitet: // ------------------------------------------hier war ich
		//DDRC |= (1<<1);
		//PORTC |= (1<<1);

/*
	while(1){
		_delay_ms(1000);
		PORTB |= (1<<PB3);
		PORTB |= (1<<PB2);
		_delay_ms(1000);
		PORTB &= ~ (1<<PB3);
		PORTB &= ~ (1<<PB2);

	}
*/


	while(1){//Dauerablauf
		showtime(stunden, minuten);

		//Uhrzeit erhhen testweise
		_delay_ms(1000);
		minuten++;
		if(minuten>=60){minuten=0;stunden++;}
		if(stunden>=13){stunden=1;}
		//ende Uhrzeit Testweise erhhen

	}
}

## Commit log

2015-10-30 Lasterhaft Wordclock erstellt
2015-11-01 Beginn Pflichtenheft
2015-11-02 Pflichten aufgelistet
2015-11-06 Beginn CAD Design
2015-11-06 Frontplatte erstellt
2015-11-06 Gehäuse erstellt
    Gehäuse erstellt, Wanddicke und Tiefe können nachträglich geändert
    werden
2015-11-06 Zwischenplatte erstellt
2015-11-06 Pflichtenheft strukturiert
2015-11-06 Pflichtenheft erweitert
2015-11-09 Ideen zu Interrupts für Ansteuerung hinzugefügt
2015-11-11 Pflichtenheft Latex angepasst
2015-11-13 Pflichtenheft wurde geordnet
2015-11-16 Erste Versuche in Eagle
2015-11-16 Bilder hochladen
2015-11-16 Bibliographie angepasst
2015-11-16 CAD Zwischenplatte angepasst
2015-11-19 RTC in Eagle Bibliothek aufgenommen
2015-11-20 CAD Design angepasst
2015-11-27 Eagle Adafruit added
2015-11-27 Eagle Hilfen hinzugefügt
2015-11-28 Eagle Schaltplan verändert
2015-12-02 Eagle Fehler verbessert
2015-12-04 Eagle Änderung
2015-12-05 Eagel WS2812 added
2015-12-07 WS2812 Layout versucht
2015-12-09 Frontplatte in Inkscape erstellt
2015-12-09 CAD Frontplattendesign eingefügt
2015-12-12 Wordclock Matrix gelayoutet
    Matrix alle Zeilen einzeln gelautet, Zeilen sind noch nicht verbunden
2015-12-15 Eagle Layout geroutet
2015-12-16 Eagle VDD gelayoutet und vieles mehr
2015-12-17 layout der leds
2015-12-19 Eagle untere hälfte der Platine und LED Layout fertig
2015-12-19 Layout fertig
2015-12-19 Dateien aufgeräumt und in Eagle Schrift hinzugefügt
2015-12-20 Schutzwiderstand für WS2812 added
2015-12-23 CAD Platine erstellt und Bauteile eingefügt
2015-12-23 Datenblätter AVR hinzugefügt
2015-12-23 Platine in CAD komplett mit Bauteilen
2015-12-23 Bohrung in Zwischenplatte hinzugefügt
    Bohrung in Zwischenplatte hinzugefügt um Platine mit Gehäuse und
    Zwischenplatte zu verbinden.
2015-12-24 Beginn des Gehäuses und anpassen der zwischenplatte
2015-12-24 Befestigung Platine und Gehäuse
    außerdem Bilder gemacht
2015-12-27 Ausschnitt USB Stecker
2015-12-27 Ausschnitte in Rückseite hinzugefügt
2015-12-27 SCL/SDA Pullups hinzugefügt
    ACHTUNG!!! Diese Pullups sind auf der ersten Platine noch nicht
    enthalten
2015-12-28 Bauteilewerte eingefügt
2015-12-28 weiter Bauteilewerte angepasst
2015-12-28 Eagle: Pullups I2C geroutet und Befestigungslöcher auf 3,2 angepasst
    Bohrergröße für Platine nun M3 fein nach Tabelle unter
    https://de.wikipedia.org/wiki/Metrisches_ISO-Gewinde
    Pullup_SCL und Pullup_SDA nun im Layout eingefügt
2015-12-29 Bauteilliste exportiert
2015-12-29 Bauteilliste ergänzt
2015-12-30 Bauteilliste erweitert mit Links
2015-12-30 Bauteilliste vervollständigt
2015-12-30 WS2812 auf Ausführung mit Schwarzer Vorderseite geändert
2015-12-30 Bestellung bei Reichelt und WS2812 und Kondensator auf 15p geändert
    Bestellung bei Reichelt und WS2812 und Wert des Kondensator am AVR
    Quarz auf 15p geändert
2015-12-31 Rechnungen entfernt
2015-12-31 Revert "Rechnungen entfernt"
    This reverts commit e376678a5a69d8bc6bf5d32d9ec70430a3809910.
2015-12-31 Ansteuerung zur Bibliografie hinzugefügt
2016-01-08 Platine in CAD aktualisiert und Bohrungsmaße gespeichert
    Die Platine im CAD Programm wurde aktualisiert und es wurde eine
    Zeichnung zum erstellen der Bohrungen in der Platine angefertigt.
2016-01-08 Gehäusebox erstellt
    Gehäusebox mit Hilfe von Boxmaker erstellt und Ausschnitte hinzugefügt
2016-01-08 Zwischenplatte in Illustrator für LaserCutter vorbereitet
2016-01-08 Zwischenplatte und Box für Lasercutter vorbereitet
2016-01-08 Frontplatte Binärclock erstellt
2016-01-13 Falscher Ausschnitt für USB in Box verbessert
2016-01-13 Lötschablone erstellt
2016-01-15 CAD Distanzhülse eingebaut
2016-01-15 AVR Studio Projekt eröffnet
2016-01-18 Rechnungen eingefügt
2016-01-18 light_ws2812 Dateien hinzugefügt
2016-01-18 Versuch AVR Studio
2016-01-18 Projektpräsentation erstellt
2016-01-18 Präsentation erweitert
2016-01-18 Eclipse Projekt eröffnet
2016-01-18 Projektpräs. angepasst
2016-01-19 Dokumentationen verschoben
2016-01-20 Frontplatten für erstellen mit Drucker
2016-01-20 Eclipse
2016-01-20 Software erste Änderungen
2016-01-23 kleine Änderungen Eclipse
2016-01-24 Eclipse erste Testversion
2016-01-24 erste Testversion nochmal neu gestepiechert
2016-01-24 Erster Software Test - Minutenlauf stimmt
2016-01-24 Buzzer getestet
2016-01-24 Beginn Test mit N Mosefet
    evtl muss N gegen P ersetz werden
2016-01-27 Versuch Matrix zu aktivieren + Begin Dokumentation
    Die Dokumentation begonnen und versuch die WS2812 anzusteuern
    Mostet getauscht gegen p-Kanal
2016-01-27 Versuch den Fehler zu finden warum nur erste LED geht
    Versuch den Fehler zu finden warum nur erste LED geht indem ich die
    Beispiele der WS2812 lib einspiele (nicht funktioniert bis jetzt
2016-01-28 Matrix Ansteuerung: alle Daten für Uhrzeit eingegeben
2016-01-28 Matrix Test hinzugefügt
2016-01-29 Wordclock läuft, noch leichte Timeprobleme
    Wordclock läuft, noch leichte Timeprobleme wegen fehlender
    Kondensatoren und leeren der Matrix; Mehrere Testroutinen eingefügt
    (auskommentiert)
2016-02-01 Versuch RT mit DS1307 lib anzusteuern
2016-02-01 Testrutinen ausgelagert in eigene Fkts
2016-02-01 Test mit DS1307 lib funktioniert
    Test mit DS1307 lib funktioniert; muss noch eingefügt werden.
2016-02-01 Projektdokumentation erweitert
2016-02-01 AVR Studio Projekt erntfernt
2016-02-01 Dokumentation Seite 4
2016-02-03 Projektdokumentation fertig
2016-02-03 Gesamtausgaben berechnet
2016-02-03 Verbesserungen Projektdokumentation 1
2016-02-03 Verbesserungen Dokumentation
2016-02-04 weitere Verbesserungen Doku
2016-02-04 Präsentation gemacht und Daten Lasercutter
2016-02-04 Punkt in Doku verbessert
2016-02-08 Notiz Lasercutter für Frontplatte
2016-02-19 DS1307 Datenblatt hinzugefügt
2016-02-19 Gesamtausgaben
2016-04-05 Beginn umschreiben der Lib ds1307 um ds1337 verwenden zu können
2016-04-05 Log Datei vergessen zu comitten

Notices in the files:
parts and their libraries:
eagle-library-edeca.net-v5: This is v1 and is licensed under the Creative Commons (Attribution-Non-Commercial-Share Alike 2.0 UK)
